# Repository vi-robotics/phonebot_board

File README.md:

# phonebot_board

The main PhoneBot electrical board containing servo control, regulator, charging and wireless capability.

This repository consists of two main components: design and firmware. The design folder contains the KiCAD design files, and the firmare folder contains the firmware meant to run on the design. Relevant documentation is located in each folder's README.md

- [Design](/design/README.md)
- [Firmware](/firmware/README.md)

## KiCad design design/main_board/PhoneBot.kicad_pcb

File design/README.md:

# Phonebot Board

For detailed information on how to assemble PhoneBot, see the [electrical getting started](https://github.com/vi-robotics/phonebot_docs/blob/main/electrical/getting_started.md).

KiCad project for Phonebot electrical schematics and layout. There are two boards for PhoneBot

- [Main Board](main_board)
  - Contains the BLE coms module, AtMEGA32u4, and servo drivers
- [Servo Board](servo_board)
  - Convenience board to make servos replaceable without soldering on the main board

Design documents are availiable for the current release.

- [Schematics](figs/Schematics.pdf)
- [Layout](figs/Layout.pdf)

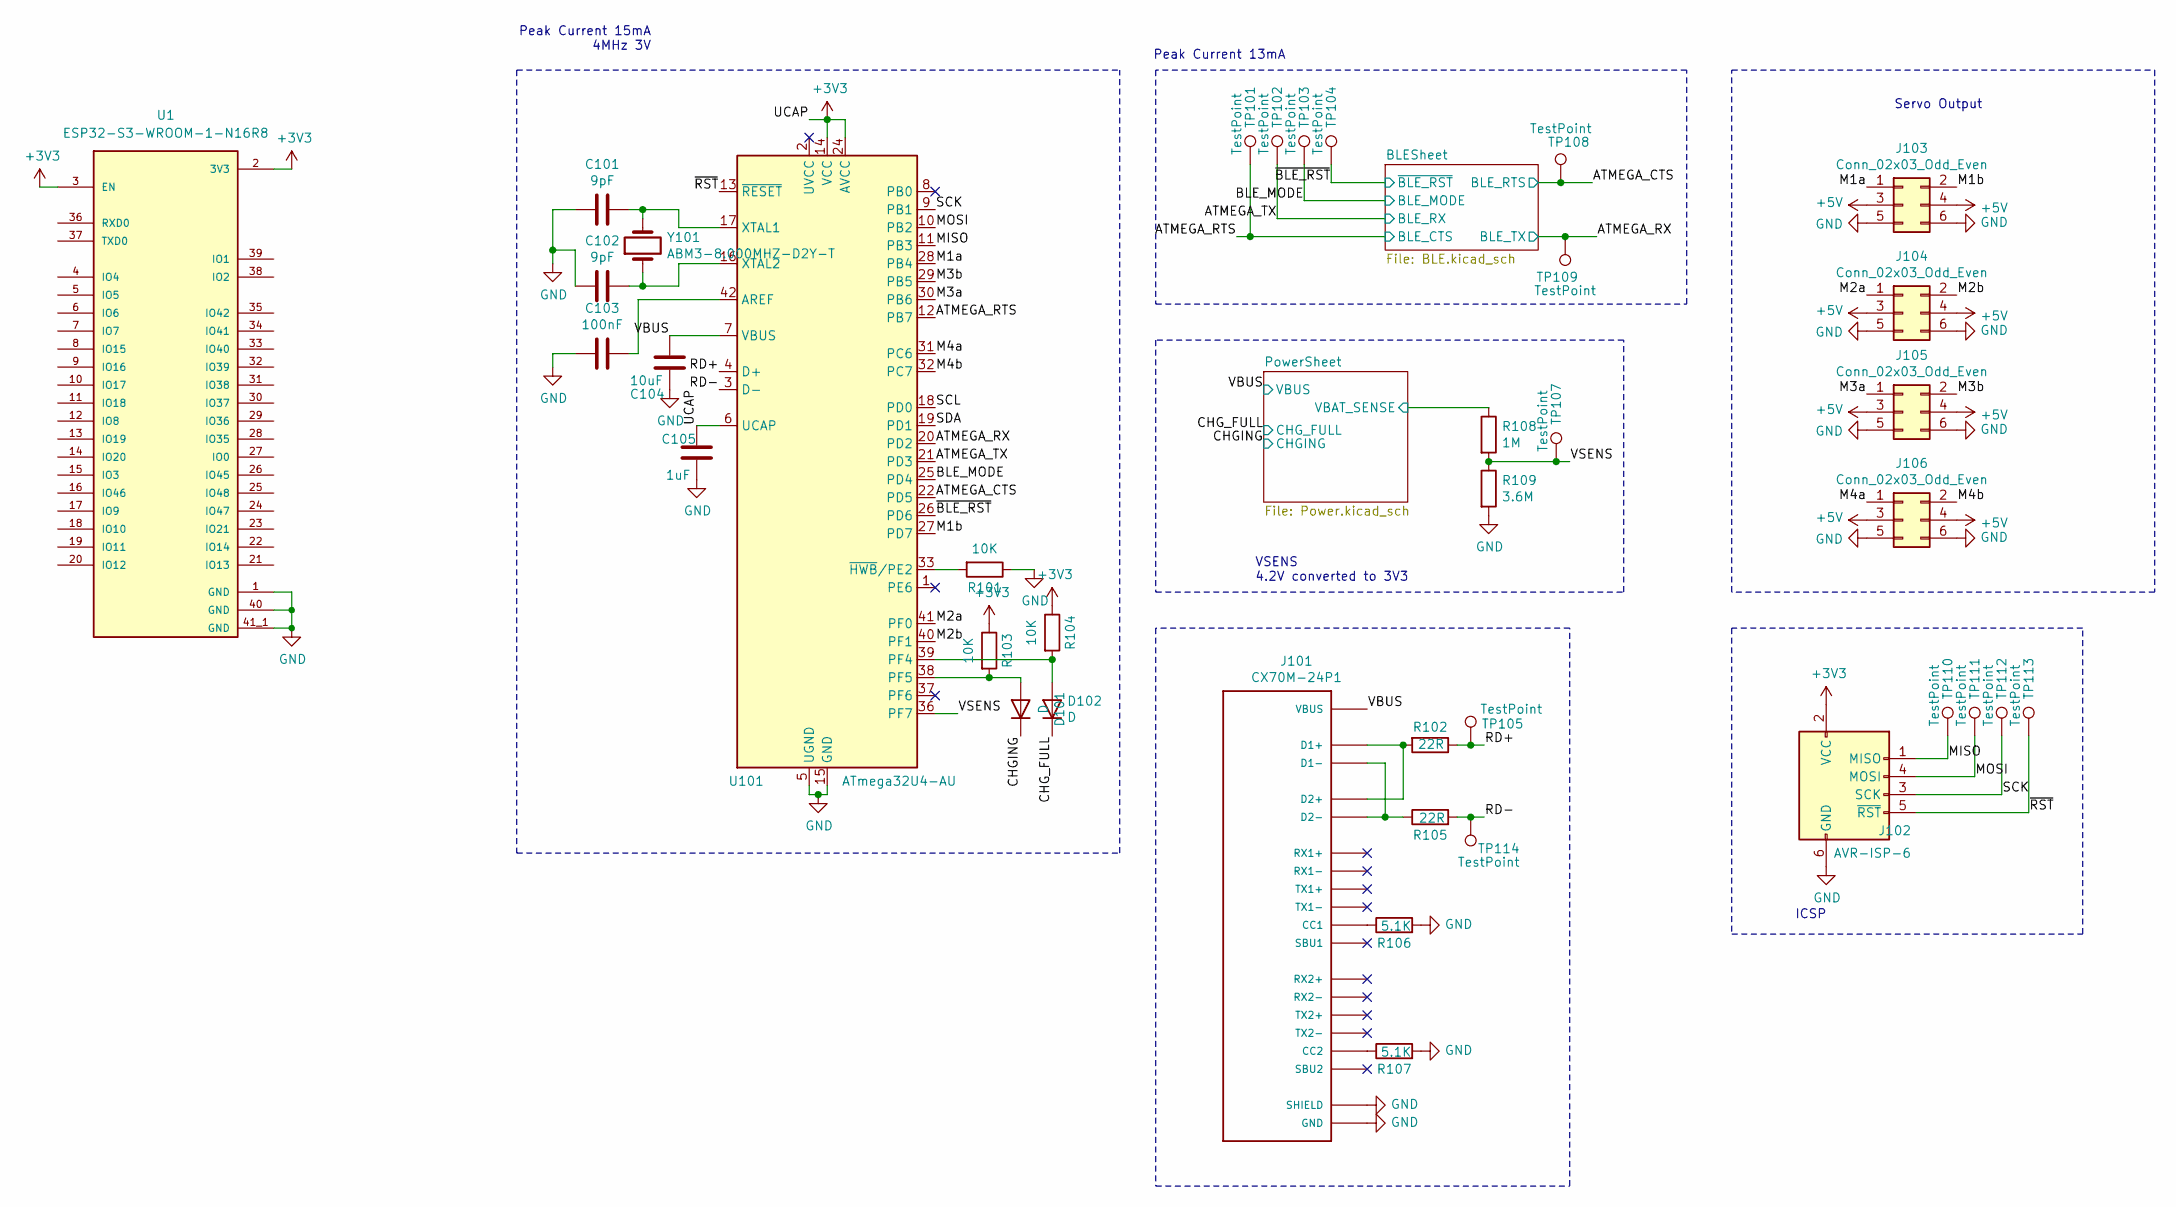
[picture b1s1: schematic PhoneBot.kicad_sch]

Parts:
C101, C102: 9pF; C_0603_1608Metric
C103: 100nF; C_0603_1608Metric
C104: 10uF; C_0603_1608Metric
C105: 1uF; C_0603_1608Metric
D101, D102: D; D_0603_1608Metric
J101: CX70M-24P1; HRS_CX70M-24P1
J102: AVR-ISP-6; PinHeader_2x03_P2.54mm_Vertical
J103, J104, J105, J106: Conn_02x03_Odd_Even; PinHeader_2x03_P2.00mm_Vertical
R101, R103, R104: 10K; R_0603_1608Metric
R102, R105: 22R; R_0603_1608Metric
R106, R107: 5.1K; R_0603_1608Metric
R108: 1M; R_0603_1608Metric
R109: 3.6M; R_0603_1608Metric
TP101, TP102, TP103, TP104, TP105, TP107, TP108, TP109, TP110, TP111, TP112, TP113, TP114: TestPoint; TestPoint_Pad_D1.0mm
U1: ESP32-S3-WROOM-1-N16R8; XCVR_ESP32-S3-WROOM-1-N16R8; PARTREV v1.0
U101: ATmega32U4-AU; TQFP-44_10x10mm_P0.8mm
Y101: ABM3-8.000MHZ-D2Y-T; Crystal_SMD_Abracon_ABM3-2Pin_5.0x3.2mm

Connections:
+3V3: C105.2, J102.2 (VCC), R103.1, R104.1, U1.2 (3V3), U1.3 (EN), U101.6 (UCAP), U101.14 (VCC), U101.24 (AVCC), U101.34 (VCC), U101.44 (AVCC); also elsewhere on the board
+5V: J103.3, J103.4, J104.3, J104.4, J105.3, J105.4, J106.3, J106.4; also elsewhere on the board
/ATMEGA_CTS: TP108.1, U101.22 (PD5); also elsewhere on the board
/ATMEGA_RTS: TP101.1, U101.12 (PB7); also elsewhere on the board
/ATMEGA_RX: TP109.1, U101.20 (PD2); also elsewhere on the board
/ATMEGA_TX: TP102.1, U101.21 (PD3); also elsewhere on the board
/BLE_MODE: TP103.1, U101.25 (PD4); also elsewhere on the board
/CHGING: D101.1 (K); also elsewhere on the board
/CHG_FULL: D102.1 (K); also elsewhere on the board
/M1a: J103.1, U101.28 (PB4)
/M1b: J103.2, U101.27 (PD7)
/M2a: J104.1, U101.41 (PF0)
/M2b: J104.2, U101.40 (PF1)
/M3a: J105.1, U101.30 (PB6)
/M3b: J105.2, U101.29 (PB5)
/M4a: J106.1, U101.31 (PC6)
/M4b: J106.2, U101.32 (PC7)
/MISO: J102.1 (MISO), TP110.1, U101.11 (PB3)
/MOSI: J102.4 (MOSI), TP111.1, U101.10 (PB2)
/PowerSheet/Vbat: R108.1; also elsewhere on the board
/RD+: R102.1, TP105.1, U101.4 (D+)
/RD-: R105.2, TP114.1, U101.3 (D-)
/SCK: J102.3 (SCK), TP112.1, U101.9 (PB1)
/SCL: U101.18 (PD0)
/SDA: U101.19 (PD1)
/VBUS: C104.2, J101.A4 (VBUS), J101.A9 (VBUS), J101.B4 (VBUS), J101.B9 (VBUS), U101.7 (VBUS); also elsewhere on the board
/VSENS: R108.2, R109.1, TP107.1, U101.36 (PF7)
/~BLE_RST: TP104.1, U101.26 (PD6); also elsewhere on the board
/~RST: J102.5 (~RST), TP113.1, U101.13 (~RESET)
GND: C101.1, C102.2, C103.2, C104.1, C105.1, J101.A1 (GND), J101.A12 (GND), J101.B1 (GND), J101.B12 (GND), J101.S1 (SHIELD), J101.S2 (SHIELD), J101.S3 (SHIELD), J101.S4 (SHIELD), J101.S5 (SHIELD), J101.S5.1 (SHIELD), J101.S6 (SHIELD), J101.S6.1 (SHIELD), J102.6 (GND), J103.5, J103.6, J104.5, J104.6, J105.5, J105.6, J106.5, J106.6, R101.1, R106.2, R107.2, R109.2, U1.1 (GND), U1.40 (GND), U1.41_1 (GND), U1.41_2 (GND), U1.41_3 (GND), U1.41_4 (GND), U1.41_5 (GND), U1.41_6 (GND), U1.41_7 (GND), U1.41_8 (GND), U1.41_9 (GND), U101.5 (UGND), U101.15 (GND), U101.23 (GND), U101.35 (GND), U101.43 (GND); also elsewhere on the board
unnamed: C101.2, U101.17 (XTAL1), Y101.2
unnamed: C102.1, U101.16 (XTAL2), Y101.1
unnamed: C103.1, U101.42 (AREF)
unnamed: D101.2 (A), R103.2, U101.38 (PF5)
unnamed: D102.2 (A), R104.2, U101.39 (PF4)
unnamed: J101.A5 (CC1), R106.1
unnamed: J101.A6 (D1+), J101.B6 (D2+), R102.2
unnamed: J101.A7 (D1-), J101.B7 (D2-), R105.1
unnamed: J101.B5 (CC2), R107.1
unnamed: R101.2, U101.33 (~HWB/PE2)

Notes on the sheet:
Servo Output
ICSP
Peak Current 15mA 4MHz 3V
Peak Current 13mA
VSENS 4.2V converted to 3V3

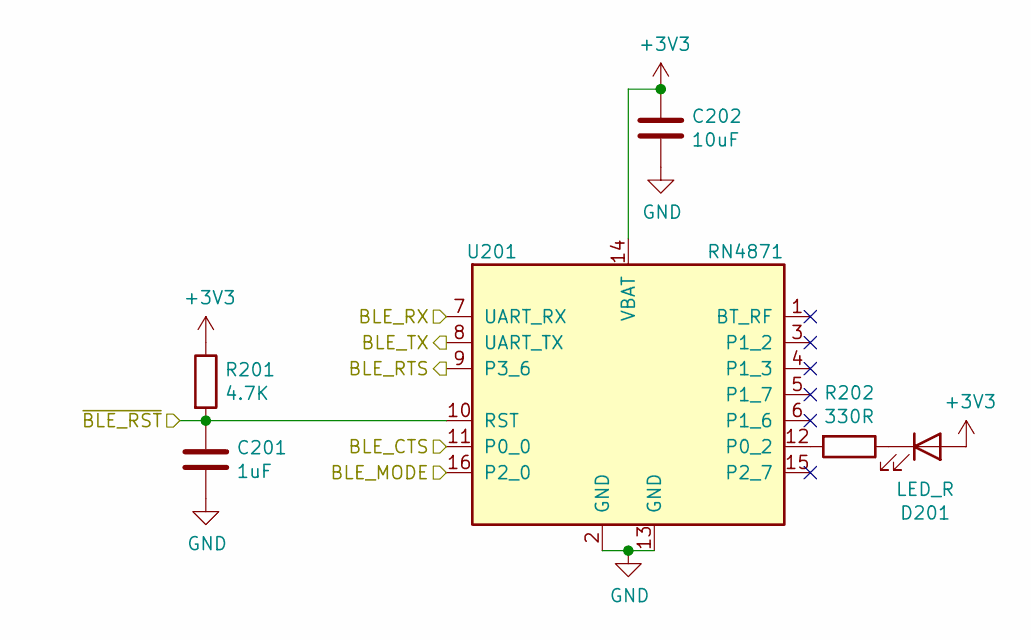
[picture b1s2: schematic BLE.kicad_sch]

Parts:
C201: 1uF; C_0603_1608Metric
C202: 10uF; C_0603_1608Metric
D201: LED_R; LED_0603_1608Metric
R201: 4.7K; R_0603_1608Metric
R202: 330R; R_0603_1608Metric
U201: RN4871; XCVR_RN4871-V%2fRM118

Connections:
+3V3: C202.1, D201.2 (A), R201.1, U201.14 (VBAT); also elsewhere on the board
/ATMEGA_CTS: U201.9 (P3_6); also elsewhere on the board
/ATMEGA_RTS: U201.11 (P0_0); also elsewhere on the board
/ATMEGA_RX: U201.8 (UART_TX); also elsewhere on the board
/ATMEGA_TX: U201.7 (UART_RX); also elsewhere on the board
/BLE_MODE: U201.16 (P2_0); also elsewhere on the board
/~BLE_RST: C201.1, R201.2, U201.10 (RST); also elsewhere on the board
GND: C201.2, C202.2, U201.2 (GND), U201.13 (GND); also elsewhere on the board
unnamed: D201.1 (K), R202.1
unnamed: R202.2, U201.12 (P0_2)

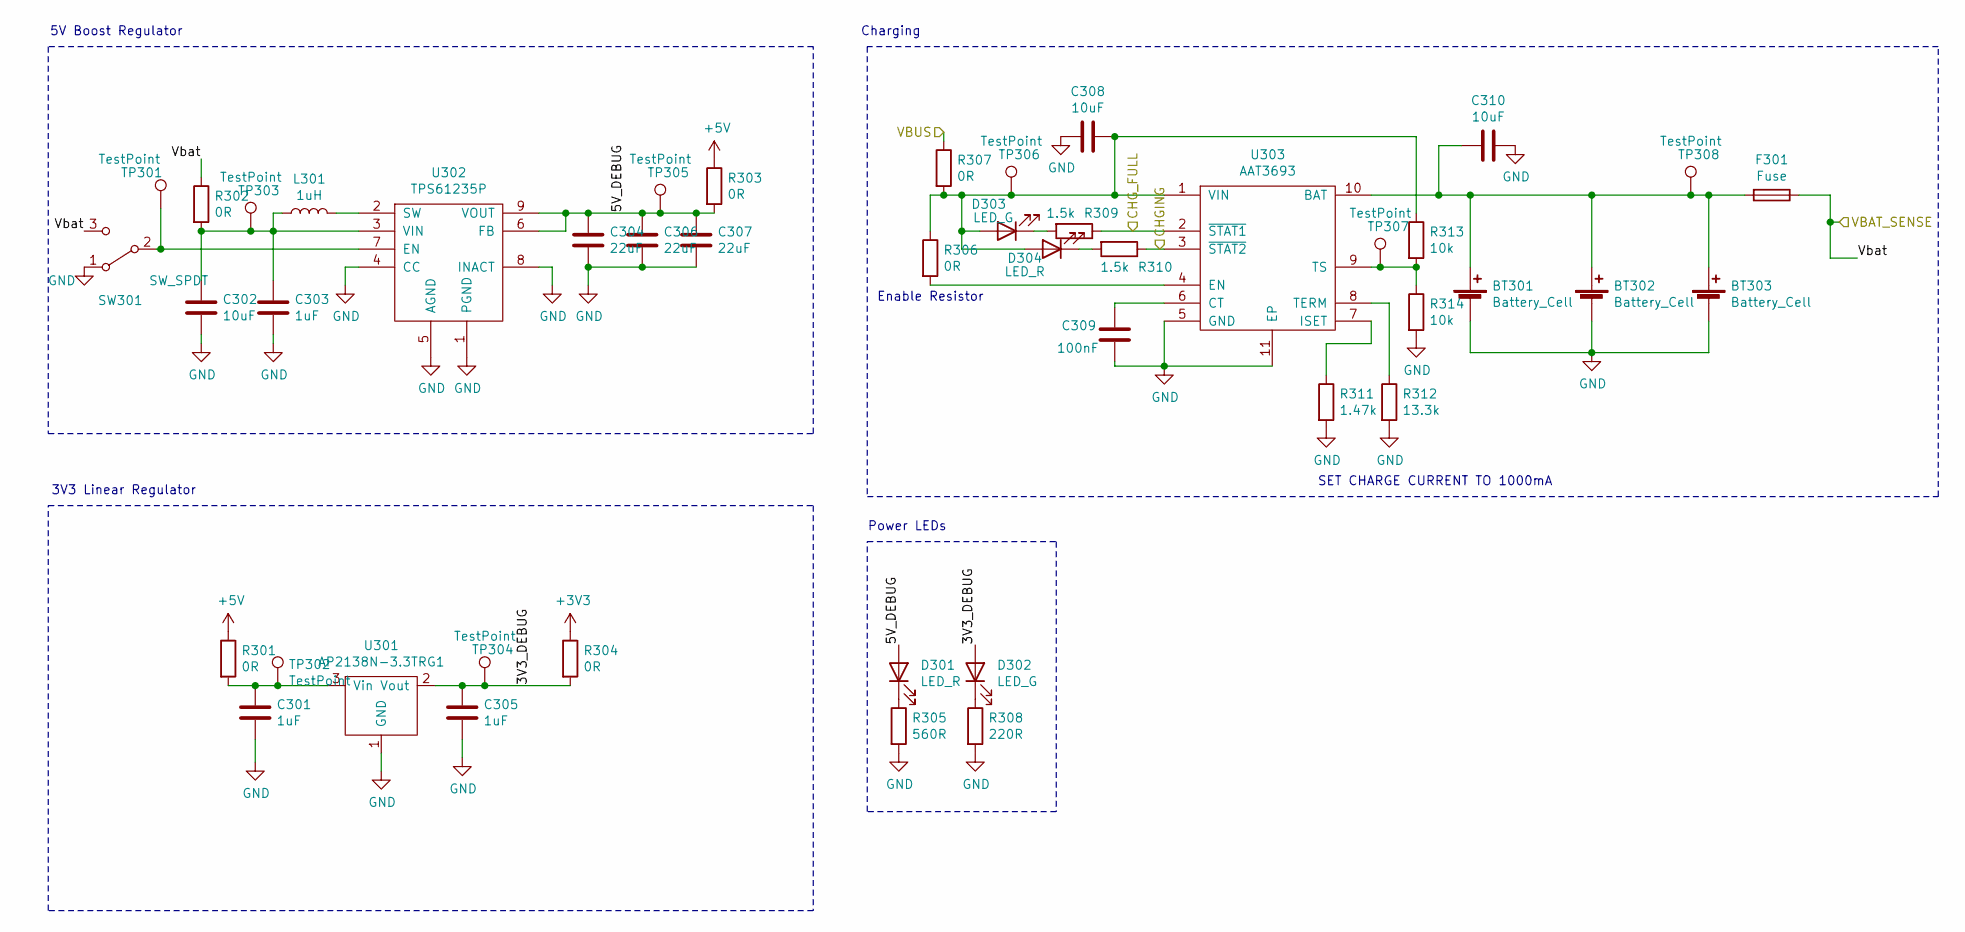
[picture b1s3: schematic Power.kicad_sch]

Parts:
BT301, BT302, BT303: Battery_Cell; JST_PH_B2B-PH-K_02x2.00mm_Straight
C301, C303, C305: 1uF; C_0603_1608Metric
C302, C308, C310: 10uF; C_0603_1608Metric
C304, C306, C307: 22uF; C_0603_1608Metric
C309: 100nF; C_0603_1608Metric
D301, D304: LED_R; LED_0603_1608Metric
D302, D303: LED_G; LED_0603_1608Metric
F301: Fuse; Fuse_0603_1608Metric
L301: 1uH; L_Taiyo-Yuden_MD-4040
R301, R304, R306: 0R; R_0603_1608Metric
R302, R303, R307: 0R; R_1206_3216Metric
R305: 560R; R_0603_1608Metric
R308: 220R; R_0603_1608Metric
R309, R310: 1.5k; R_0603_1608Metric
R311: 1.47k; R_0603_1608Metric
R312: 13.3k; R_0603_1608Metric
R313, R314: 10k; R_0603_1608Metric
SW301: SW_SPDT; SW_SPDT_1825232
TP301, TP302, TP303, TP304, TP305, TP306, TP307, TP308: TestPoint; TestPoint_Pad_D1.0mm
U301: AP2138N-3.3TRG1; SOT-23
U302: TPS61235P; TPS61235PRWLT
U303: AAT3693

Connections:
+3V3: R304.1; also elsewhere on the board
+5V: R301.1, R303.1; also elsewhere on the board
/CHGING: R310.1, U303.3 (~STAT2); also elsewhere on the board
/CHG_FULL: R309.1, U303.2 (~STAT1); also elsewhere on the board
/PowerSheet/3V3_DEBUG: C305.1, D302.2 (A), R304.2, TP304.1, U301.2 (Vout)
/PowerSheet/5V_DEBUG: C304.1, C306.1, C307.1, D301.2 (A), R303.2, TP305.1, U302.6 (FB), U302.9 (VOUT)
/PowerSheet/Vbat: F301.1, R302.1, SW301.3 (C); also elsewhere on the board
/VBUS: R307.1; also elsewhere on the board
GND: BT301.2 (-), BT302.2 (-), BT303.2 (-), C301.2, C302.2, C303.2, C304.2, C305.2, C306.2, C307.2, C308.2, C309.2, C310.1, R305.2, R308.2, R311.2, R312.2, R314.2, SW301.1 (A), U301.1 (GND), U302.1 (PGND), U302.4 (CC), U302.5 (AGND), U302.8 (INACT), U303.5 (GND), U303.11 (EP); also elsewhere on the board
unnamed: BT301.1 (+), BT302.1 (+), BT303.1 (+), C310.2, F301.2, TP308.1, U303.10 (BAT)
unnamed: C301.1, R301.2, TP302.1, U301.3 (Vin)
unnamed: C302.1, C303.1, L301.1, R302.2, TP303.1, U302.3 (VIN)
unnamed: C308.1, D303.2 (A), D304.2 (A), R306.1, R307.2, R313.1, TP306.1, U303.1 (VIN)
unnamed: C309.1, U303.6 (CT)
unnamed: D301.1 (K), R305.1
unnamed: D302.1 (K), R308.1
unnamed: D303.1 (K), R309.2
unnamed: D304.1 (K), R310.2
unnamed: L301.2, U302.2 (SW)
unnamed: R306.2, U303.4 (EN)
unnamed: R311.1, U303.7 (ISET)
unnamed: R312.1, U303.8 (TERM)
unnamed: R313.2, R314.1, TP307.1, U303.9 (TS)
unnamed: SW301.2 (B), TP301.1, U302.7 (EN)

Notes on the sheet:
Power LEDs
5V Boost Regulator
SET CHARGE CURRENT TO 1000mA
3V3 Linear Regulator
Charging
Enable Resistor

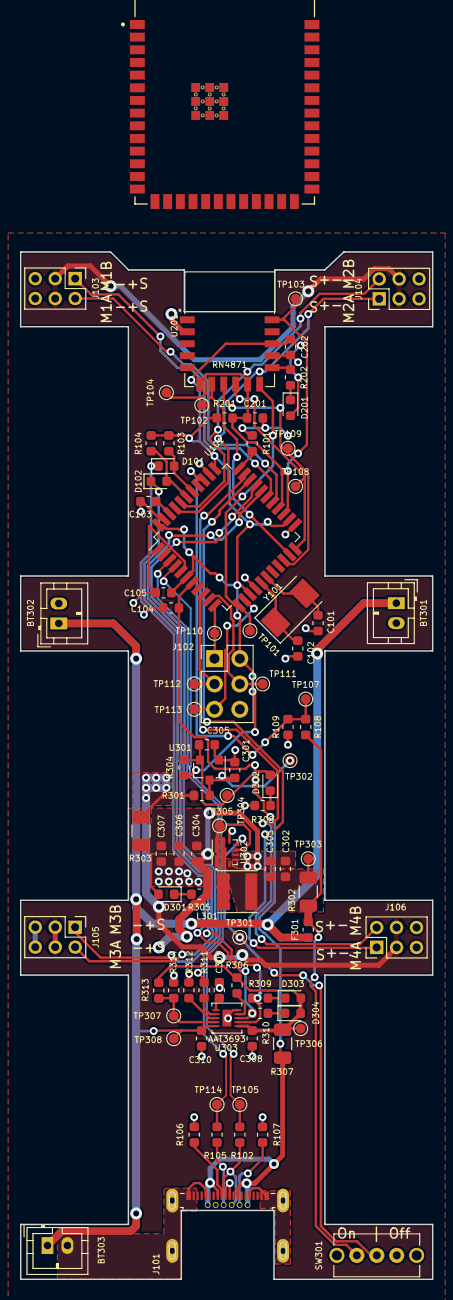
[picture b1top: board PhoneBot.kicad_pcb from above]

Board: 2 copper layers, 41.3 x 103.0 mm, 89 parts (0 on the bottom side), 57 nets.

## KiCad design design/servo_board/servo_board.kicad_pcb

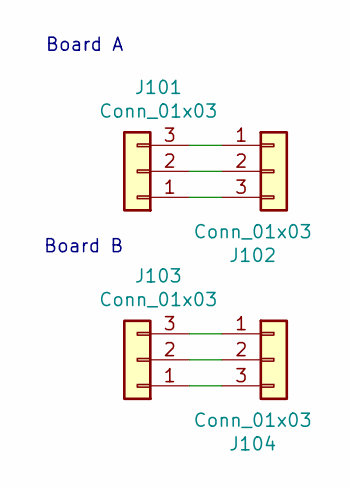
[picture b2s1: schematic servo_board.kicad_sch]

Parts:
J101, J103: Conn_01x03; PinHeader_1x03_P2.00mm_Horizontal
J102, J104: Conn_01x03; PinHeader_1x03_P2.00mm_Vertical

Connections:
unnamed: J101.1, J102.3
unnamed: J101.2, J102.2
unnamed: J101.3, J102.1
unnamed: J103.1, J104.3
unnamed: J103.2, J104.2
unnamed: J103.3, J104.1

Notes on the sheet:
Board A
Board B

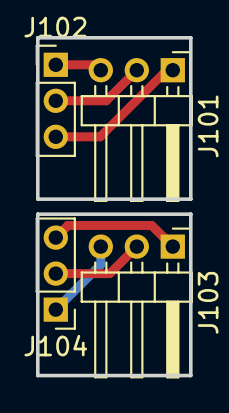
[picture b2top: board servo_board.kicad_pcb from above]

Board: 2 copper layers, 8.5 x 18.8 mm, 4 parts (0 on the bottom side), 6 nets.

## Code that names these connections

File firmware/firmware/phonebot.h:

/**
 * @file phonebot.h
 * @author Maximilian Schommer (maxschommer@gmail.com)
 * @brief PhoneBot class monitors and responds to BLE serial events
 * @version 0.1
 * @date 2021-05-11
 *
 * @copyright Copyright (c) 2021
 *
 */
#ifndef __PHONEBOT_H__
#define __PHONEBOT_H__

#include "common.h"
#include "command_interpreter.h"
#include "ble.h"

 /*
    PIN MAPPINGS
     (US)
     M1a , M1b , M2a , M2b , M3a , M3b , M4a , M4b
     PB4 , PD7 , PF0 , PF1 , PB6 , PB5 , PC6 , PC7
     (Physical Pin Number)
     28  , 27  , 41  , 40  , 30  , 29  , 31  , 32
     (Sparkfun)
     D8  , D6  , D23 , D22 , D10 , D9  , D5  , D13 // << use this since we're using their board definition
 */


 /**
  * @brief PhoneBot manages servo control and BLE communication
  *
  */
class PhoneBot
{
   int pins_[NUM_JOINTS] = { 8, 6, 23, 22, 10, 9, 5, 13 };

   // Initialize it with the default pins by default
   CommandInterpreter command_interpreter = CommandInterpreter(pins_);

   // communication
   BLE ble_;

   int positions_[NUM_JOINTS];

public:

   /**
      @brief Constructs a PhoneBot which is bound to the default pins
   */
   PhoneBot(); // Default constructor uses above pins if none are provided

   /**
      @brief Constructs a PhoneBot which is bound to the provided pins

      @param pins The pins to bind to for each leg. Must contain 8 elements
   */
   PhoneBot(const int* pins);

   /**
    * @brief Starts BLE communication
    */
   void begin();


   /**
    * @brief Handles BLE receive and transmit buffers as well as
    * interpreting data sent over BLE and executing it via the
    * command interpreter.
    */
   void step();
};

#endif

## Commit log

2021-04-01 Updated gitignore and added firmware
2021-04-01 Deleted legacy files
2021-04-03 Added servo board
2021-04-03 Removed backup
2021-04-03 removed all backups
2021-04-05 Removed more spurious files and made README more readble
2021-05-12 Moved intialization of command interpreter to inside PhoneBot
2021-05-12 Reformatted files according to Arduino's preferences
2021-05-12 Removed empty walk file
2021-05-12 Made comments consistent, broke all lone header files into header and cpp files
2021-05-12 Cleaned up docs a bit
2021-05-12 Updated test_walk.ino to actually walk
2021-05-12 Added file headers, removed useless apps, and moved firmware apps into a subdirectory
2021-05-12 Added file header to servo_manager
2021-10-02 Update LICENSE
2022-05-09 Created esp32 footprint and symbol
2022-06-06 Schematic almost finished
2022-06-06 Added new firmware hello world for ESP32-S3
